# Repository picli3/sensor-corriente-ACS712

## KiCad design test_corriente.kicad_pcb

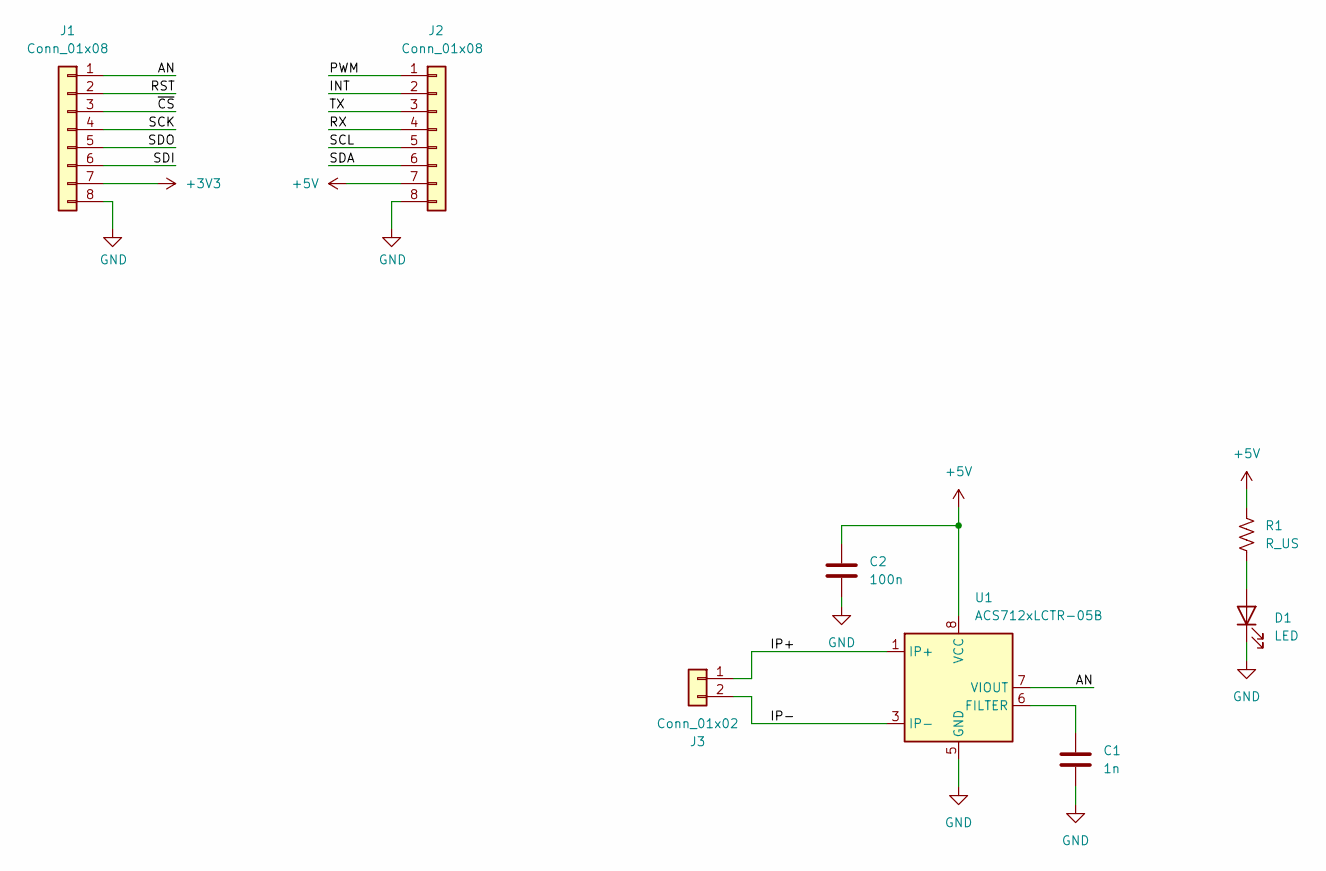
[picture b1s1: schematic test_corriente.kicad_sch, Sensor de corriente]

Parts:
C1: 1n; C_0805_2012Metric_Pad1.18x1.45mm_HandSolder
C2: 100n; C_0805_2012Metric_Pad1.18x1.45mm_HandSolder
D1: LED; LED_0805_2012Metric_Pad1.15x1.40mm_HandSolder
J1, J2: Conn_01x08; PinHeader_1x08_P2.54mm_Vertical
J3: Conn_01x02; TerminalBlock_Phoenix_MKDS-1,5-2-5.08_1x02_P5.08mm_Horizont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
R1: R_US; R_0805_2012Metric_Pad1.20x1.40mm_HandSolder
U1: ACS712xLCTR-05B; SOIC-8_3.9x4.9mm_P1.27mm

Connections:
+3V3: J1.7
+5V: C2.1, J2.7, R1.1, U1.8 (VCC)
/AN: J1.1, U1.7 (VIOUT)
/INT: J2.2
/IP+: J3.1, U1.1 (IP+), U1.2 (IP+)
/IP-: J3.2, U1.3 (IP-), U1.4 (IP-)
/PWM: J2.1
/RST: J1.2
/RX: J2.4
/SCK: J1.4
/SCL: J2.5
/SDA: J2.6
/SDI: J1.6
/SDO: J1.5
/TX: J2.3
/~CS: J1.3
GND: C1.2, C2.2, D1.1 (K), J1.8, J2.8, U1.5 (GND)
unnamed: D1.2 (A), R1.2
unnamed: C1.1, U1.6 (FILTER)

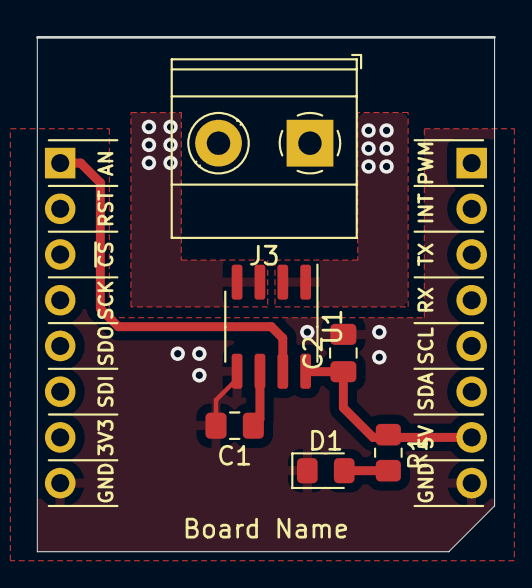
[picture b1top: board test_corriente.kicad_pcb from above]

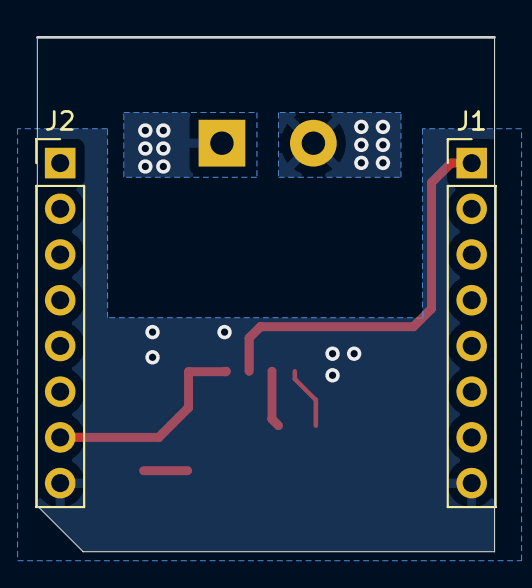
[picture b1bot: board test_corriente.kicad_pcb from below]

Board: 2 copper layers, 25.4 x 28.5 mm, 8 parts (2 on the bottom side), 7 nets.

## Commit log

2021-07-21 mikroBUS board, with pins & nets
2023-08-17 actualizando a kicad 7
2023-08-17 sensor terminado
